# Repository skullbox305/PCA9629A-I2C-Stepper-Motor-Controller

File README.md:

# PCA9629A I²C Stepper Motor Controller Breakout Board 

- ## Features

  - NXP PCA9629A I²C Stepper Controller
  - Allegro A3909 Dual Full Bridge Motor Driver
  - Maxim Integrated MAX17291 5.5V Boost Converter powering the controller and motor (can be deselected through a jumper to power a motor up to 18V)

- ## ToDo
  - Boost converter is very weak. Replace for another with higher current.

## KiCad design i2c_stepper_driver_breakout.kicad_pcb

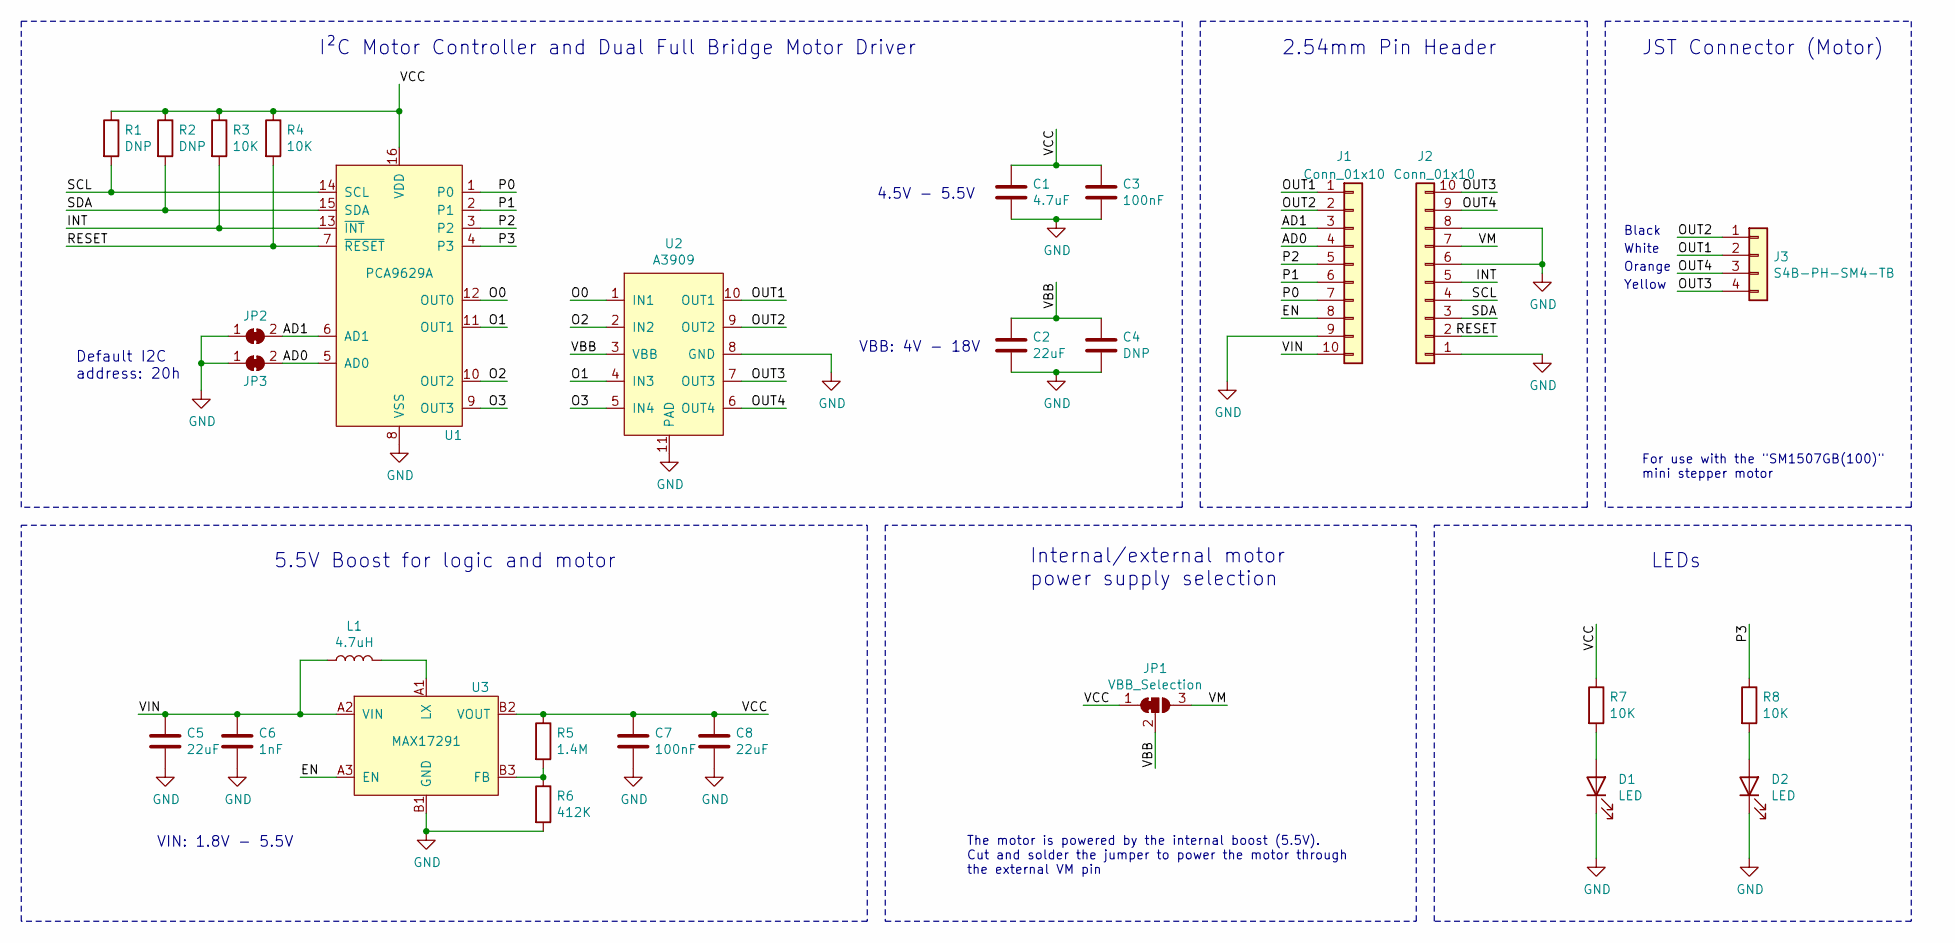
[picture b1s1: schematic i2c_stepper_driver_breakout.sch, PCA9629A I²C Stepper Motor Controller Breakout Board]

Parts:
C1: 4.7uF; C_0402_1005Metric; MPN C1005X5R1A475K050BC
C2, C5, C8: 22uF; C_0805_2012Metric; MPN CL21A226MAYNNNE
C3, C7: 100nF; C_0402_1005Metric; MPN GCM155R71C104JA55D
C4: DNP; C_0805_2012Metric
C6: 1nF; C_0402_1005Metric; MPN 0402YC102KAT2A
D1, D2: LED; LED_0603_1608Metric; MPN LS L29K-G1H2-1-Z
J1, J2: Conn_01x10; PinHeader_1x10_P2.54mm_Vertical
J3: S4B-PH-SM4-TB; JST_PH_S4B-PH-SM4-TB_1x04-1MP_P2.00mm_Horizontal; MPN S4B-PH-SM4-TB(LF)(SN)
JP1: VBB_Selection; SolderJumper-3_P1.3mm_Bridged2Bar12_RoundedPad1.0x1.5mm
JP2, JP3: SolderJumper_2_Bridged; SolderJumper-2_P1.3mm_Bridged2Bar_RoundedPad1.0x1.5mm
L1: 4.7uH; L_1008_2520Metric; MPN LQH2HPZ4R7MGRL
R1, R2: DNP; R_0402_1005Metric
R3, R4: 10K; R_0402_1005Metric; MPN RC0402FR-0710KL
R5: 1.4M; R_0402_1005Metric; MPN RK73H1ETTP1404F
R6: 412K; R_0402_1005Metric; MPN ERJ-2RKF4123X
R7, R8: 10K; R_0603_1608Metric; MPN AC0603JR-0710KL
U1: PCA9629A; TSSOP-16_4.4x5mm_P0.65mm; MPN PCA9629APWJ
U2: A3909; MPN A3909GLYTR-T
U3: MAX17291; MAX17291ATA+; MPN MAX17291ANT+

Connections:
/AD0: J1.4, JP3.2 (B), U1.5 (AD0)
/AD1: J1.3, JP2.2 (B), U1.6 (AD1)
/EN: J1.8, U3.A3 (EN)
/INT: J2.5, R3.2, U1.13 (~INT)
/O0: U1.12 (OUT0), U2.1 (IN1)
/O1: U1.11 (OUT1), U2.4 (IN3)
/O2: U1.10 (OUT2), U2.2 (IN2)
/O3: U1.9 (OUT3), U2.5 (IN4)
/OUT1: J1.1, J3.2, U2.10 (OUT1)
/OUT2: J1.2, J3.1, U2.9 (OUT2)
/OUT3: J2.10, J3.4, U2.7 (OUT3)
/OUT4: J2.9, J3.3, U2.6 (OUT4)
/P0: J1.7, U1.1 (P0)
/P1: J1.6, U1.2 (P1)
/P2: J1.5, U1.3 (P2)
/P3: R8.1, U1.4 (P3)
/RESET: J2.2, R4.2, U1.7 (~RESET)
/SCL: J2.4, R1.2, U1.14 (SCL)
/SDA: J2.3, R2.2, U1.15 (SDA)
/VBB: C2.1, C4.1, JP1.2 (C), U2.3 (VBB)
/VCC: C1.1, C3.1, C7.1, C8.1, JP1.1 (A), R1.1, R2.1, R3.1, R4.1, R5.1, R7.1, U1.16 (VDD), U3.B2 (VOUT)
/VIN: C5.1, C6.1, J1.10, L1.1, U3.A2 (VIN)
/VM: J2.7, JP1.3 (B)
GND: C1.2, C2.2, C3.2, C4.2, C5.2, C6.2, C7.2, C8.2, D1.1 (K), D2.1 (K), J1.9, J2.1, J2.6, J2.8, JP2.1 (A), JP3.1 (A), R6.2, U1.8 (VSS), U2.8 (GND), U2.11 (PAD), U3.B1 (GND)
unnamed: D1.2 (A), R7.2
unnamed: D2.2 (A), R8.2
unnamed: L1.2, U3.A1 (LX)
unnamed: R5.2, R6.1, U3.B3 (FB)

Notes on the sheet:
Default I2C address: 20h
2.54mm Pin Header
4.5V - 5.5V
VBB: 4V - 18V
I²C Motor Controller and Dual Full Bridge Motor Driver
JST Connector (Motor)
5.5V Boost for logic and motor
The motor is powered by the internal boost (5.5V). Cut and solder the jumper to power the motor through the external VM pin
VIN: 1.8V - 5.5V
Black
LEDs
Internal/external motor power supply selection
For use with the "SM1507GB(100)" mini stepper motor
White
Orange
Yellow

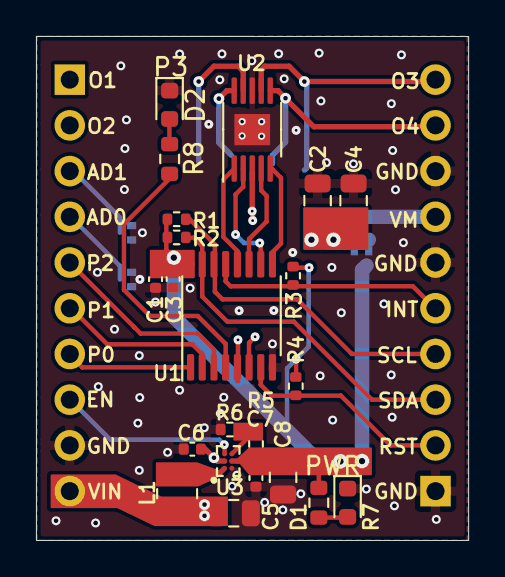
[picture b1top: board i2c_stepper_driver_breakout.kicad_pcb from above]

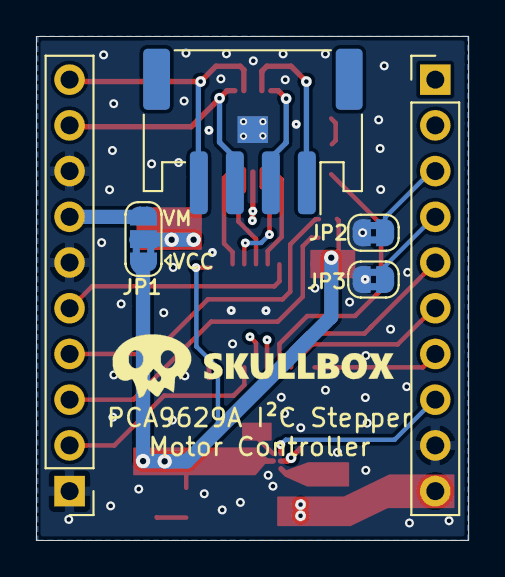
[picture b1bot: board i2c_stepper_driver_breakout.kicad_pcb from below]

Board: 4 copper layers, 24.0 x 28.0 mm, 28 parts (6 on the bottom side), 28 nets.

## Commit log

2020-12-17 Started schematic and Layout
2020-12-18 Continued layout
2020-12-19 Added boost converter, continued layout
2020-12-20 Finished schematic and layout for now
2021-01-12 Bugfixes
2021-02-01 Layout modifications due to some bugs
    h
